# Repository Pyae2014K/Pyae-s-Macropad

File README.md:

# Pyae's Macropad

My macropad is a 13 key macropad with a rotary encoder.
It uses QMK firmware

It serves as a macropad that I can use every day.

## Features:
- EC11 Rotary encoder for volume
- 13 Keys, 12 for macros and 1 for swapping layers
- [VIA](https://www.caniusevia.com/) support

## PCB
My PCB was made using KiCad.

Schematic

PCB

I used [Joe Scotto's](https://www.youtube.com/@joe_scotto) footprints for all of them.

## CAD Model
Everything fits together using 4 M3 Bolts and heatset inserts.

It has 4 different pieces, Top Case, Bottom Case, Plate, and a Rotary Encoder Knob

This model was made in Fusion 360 by Autodesk.

## Firmware
This macropad uses [QMK](https://qmk.fm/) firmware for its code.
- 13 keys; 12 for macros, 1 for layers
- Rotary encoder used to change volume

## BOM:
Here is everything that is needed to make this macropad
| Qty | Part | Description |
|-----:|------|-------------|
| 1 | Seeed XIAO RP2040 | Microcontroller |
| 13 | MX-Style Switches | Mechanical keyboard switch |
| 13 | DSA Keycaps | DSA profile keycap |
| 14 | 1N4148 Diodes | DO-35 through-hole diode |
| 1 | EC11E Rotary Encoder | Rotary encoder |
| 4 | M3x16mm Screws | M3 screw |
| 4 | M3x5mx4mm Heatset Inserts | M3 threaded heat-set insert |
| 1 | Case Top | 3D printed top case |
| 1 | Case Bottom | 3D printed bottom case |
| 1 | Plate | Switch plate |
| 1 | Knob | Rotary encoder knob |

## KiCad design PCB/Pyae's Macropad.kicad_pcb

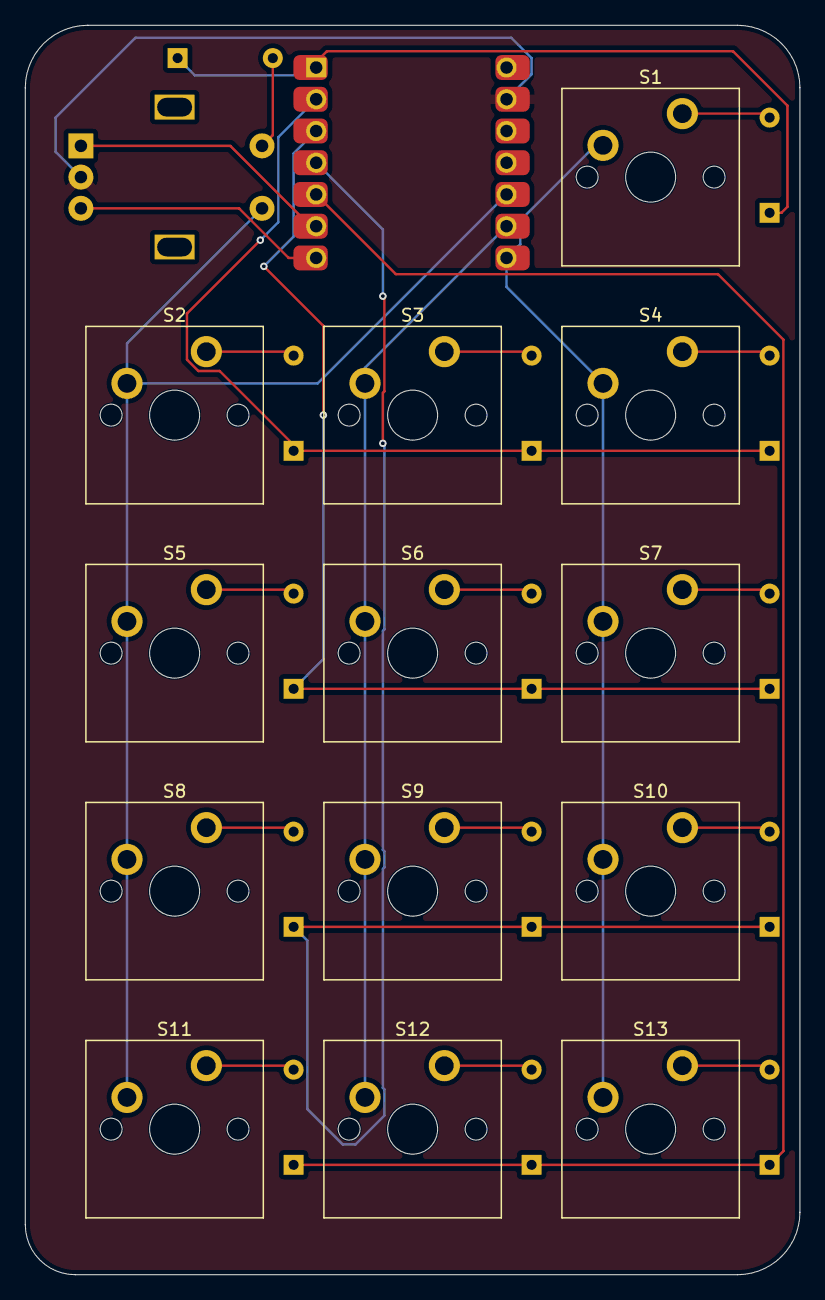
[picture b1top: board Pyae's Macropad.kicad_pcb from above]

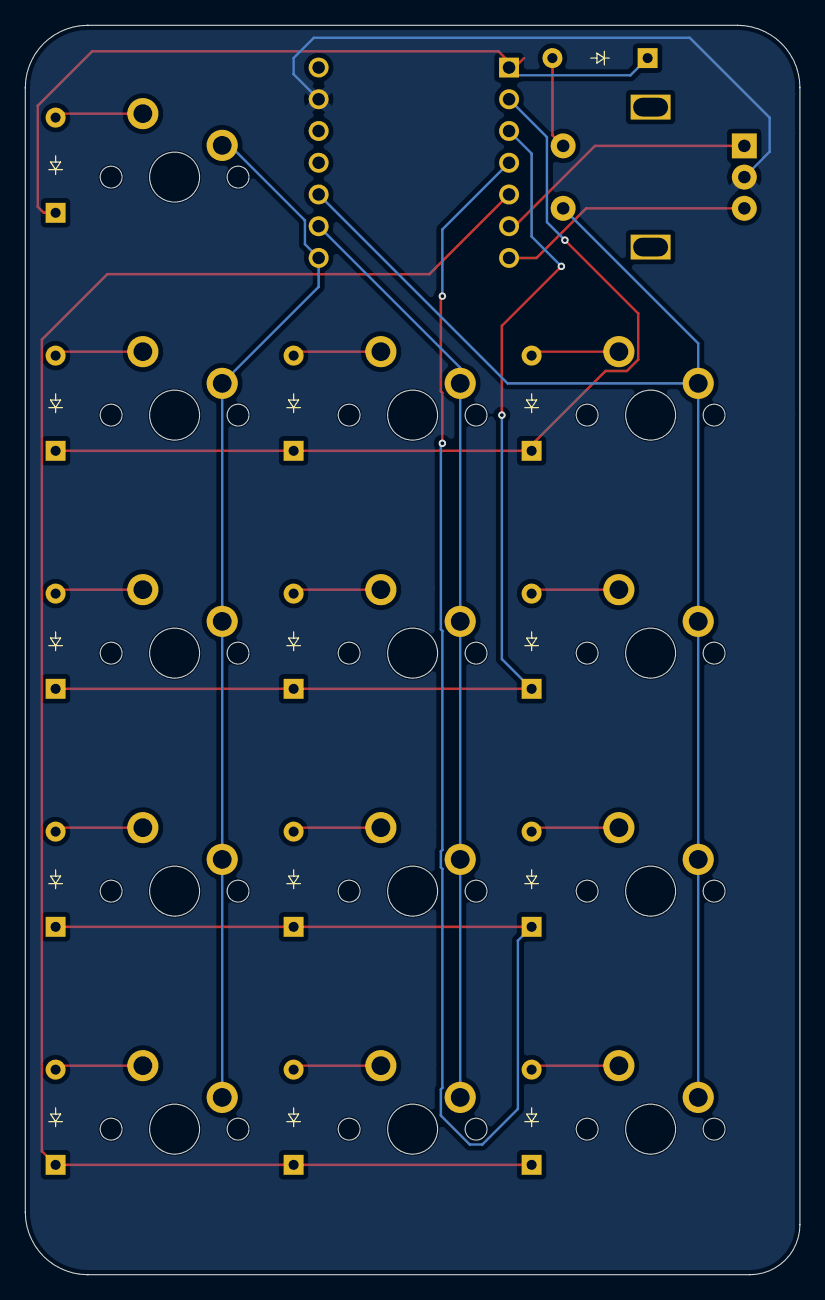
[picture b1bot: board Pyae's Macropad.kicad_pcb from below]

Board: 2 copper layers, 62.0 x 100.0 mm, 29 parts (14 on the bottom side), 25 nets.

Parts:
D1, D2, D3, D4, D5, D6, D7, D8, D9, D10, D11, D12, D13, D14: Diode_DO-35
S1, S2, S3, S4, S5, S6, S7, S8, S9, S10, S11, S12, S13: MX_PCB_1.00u
SW1: RotaryEncoder_Switch; Encoder_EC11_MX
U1: MOUDLE-SEEEDUINO-XIAO; Seeed_XIAO_RP2040

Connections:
A: SW1.A, U1.6 (PA9_A5_D5_SCL)
B: SW1.B, U1.7 (PB08_A6_D6_TX)
Col0: S2.1, S5.1, S8.1, S11.1, SW1.S1, U1.10 (PA5_A9_D9_MISO)
Col1: S3.1, S6.1, S9.1, S12.1, U1.9 (PA7_A8_D8_SCK)
Col2: S1.1, S4.1, S7.1, S10.1, S13.1, U1.8 (PB09_A7_D7_RX)
GND: SW1.C, U1.13 (GND)
unnamed: D2.2 (A), S1.2
unnamed: D3.2 (A), S2.2
unnamed: D4.2 (A), S3.2
unnamed: D5.2 (A), S4.2
unnamed: D6.2 (A), S5.2
unnamed: D7.2 (A), S6.2
unnamed: D8.2 (A), S7.2
unnamed: D9.2 (A), S8.2
unnamed: D10.2 (A), S9.2
unnamed: D11.2 (A), S10.2
unnamed: D12.2 (A), S11.2
unnamed: D13.2 (A), S12.2
unnamed: D14.2 (A), S13.2
Row0: D1.1 (K), D2.1 (K), U1.1 (PA02_A0_D0)
Row1: D3.1 (K), D4.1 (K), D5.1 (K), U1.2 (PA4_A1_D1)
Row2: D6.1 (K), D7.1 (K), D8.1 (K), U1.3 (PA10_A2_D2)
Row3: D9.1 (K), D10.1 (K), D11.1 (K), U1.4 (PA11_A3_D3)
Row4: D12.1 (K), D13.1 (K), D14.1 (K), U1.5 (PA8_A4_D4_SDA)
S2: D1.2 (A), SW1.S2

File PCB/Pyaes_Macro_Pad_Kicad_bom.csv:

Designator,Footprint,Quantity,Value,LCSC Part #
"D1, D10, D11, D12, D2, D3, D4, D5, D6, D7, D8, D9",Diode_DO-35,12,~,
J2,OLED_128x32,1,OLED_DISPLAY,
"S1, S10, S11, S12, S2, S3, S4, S5, S6, S7, S8, S9",MX_PCB_1.00u,12,~,
SW13,Encoder_EC11_MX,1,RotaryEncoder_Switch,
U1,Seeed_XIAO_RP2040,1,MOUDLE-SEEEDUINO-XIAO,

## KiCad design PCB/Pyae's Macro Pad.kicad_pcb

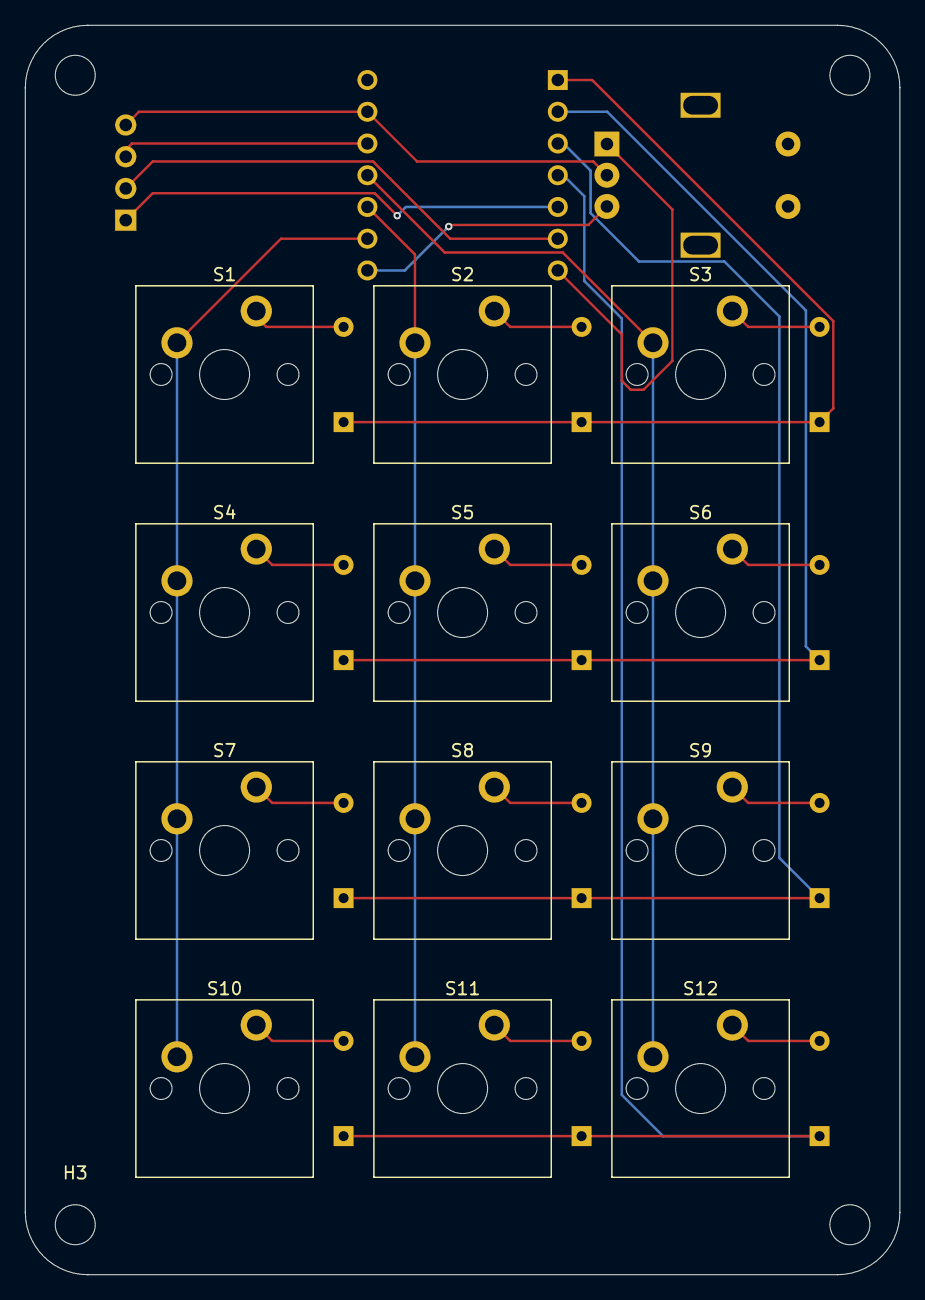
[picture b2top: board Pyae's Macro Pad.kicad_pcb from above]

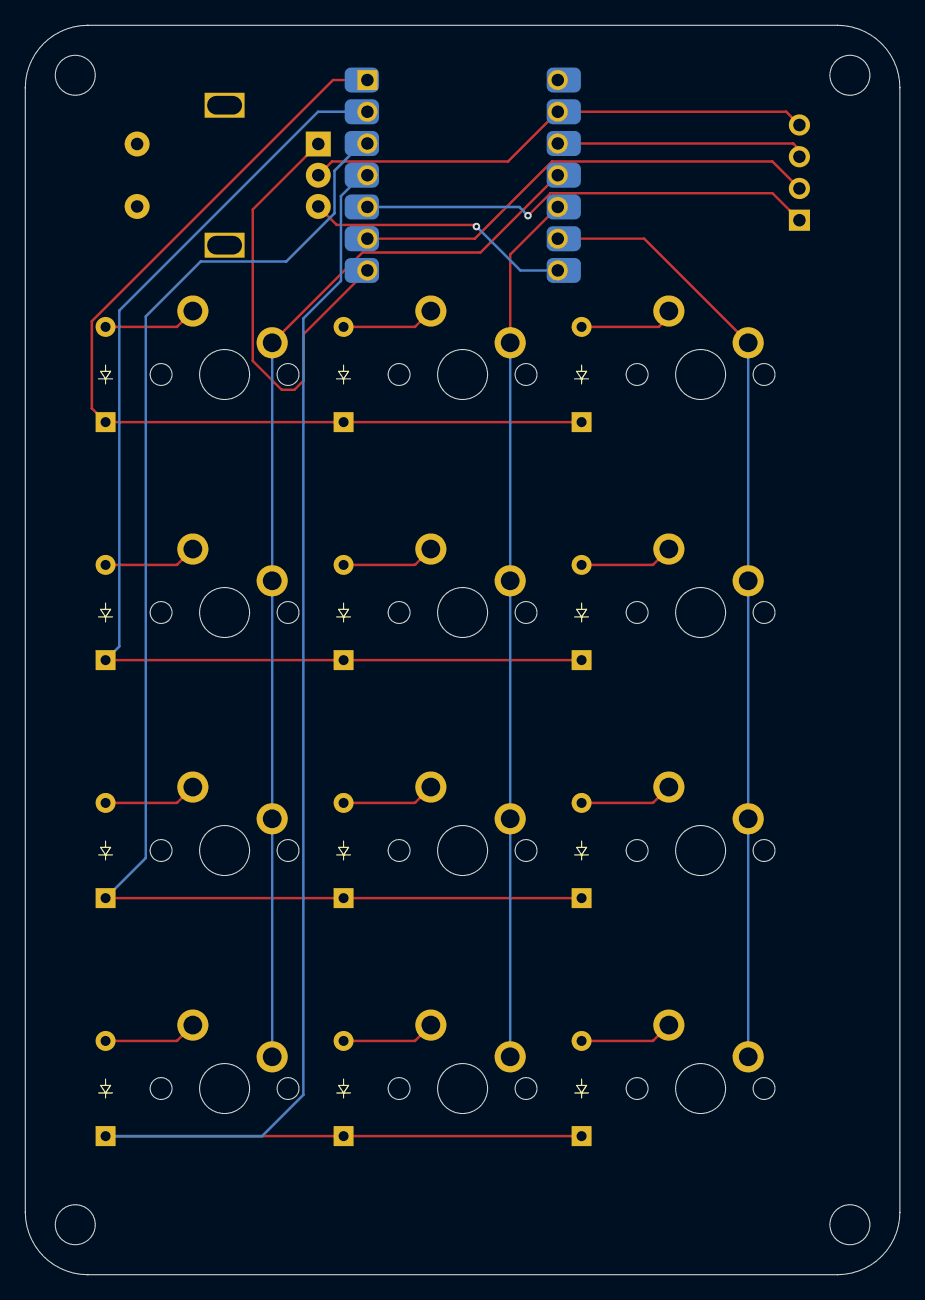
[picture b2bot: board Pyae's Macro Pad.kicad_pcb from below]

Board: 2 copper layers, 70.0 x 100.0 mm, 31 parts (13 on the bottom side), 25 nets.

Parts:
D1, D2, D3, D4, D5, D6, D7, D8, D9, D10, D11, D12: Diode_DO-35
H1, H2, H3, H4: MountingHole; MountingHole_3.2mm_M3
J2: OLED_DISPLAY; OLED_128x32
S1, S2, S3, S4, S5, S6, S7, S8, S9, S10, S11, S12: MX_PCB_1.00u
SW13: RotaryEncoder_Switch; Encoder_EC11_MX
U1: MOUDLE-SEEEDUINO-XIAO; Seeed_XIAO_RP2040

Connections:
/COL0: S1.1, S4.1, S7.1, S10.1, U1.9 (PA7_A8_D8_SCK)
/COL1: S2.1, S5.1, S8.1, S11.1, U1.10 (PA5_A9_D9_MISO)
/COL2: S3.1, S6.1, S9.1, S12.1, U1.11 (PA6_A10_D10_MOSI)
/EC11A: SW13.A, U1.7 (PB08_A6_D6_TX)
/EC11B: SW13.B, U1.8 (PB09_A7_D7_RX)
/OLED_SCL: J2.2, U1.6 (PA9_A5_D5_SCL)
/OLED_SDA: J2.1, U1.5 (PA8_A4_D4_SDA)
/ROW0: D1.1 (K), D2.1 (K), D3.1 (K), U1.1 (PA02_A0_D0)
/ROW1: D4.1 (K), D5.1 (K), D6.1 (K), U1.2 (PA4_A1_D1)
/ROW2: D7.1 (K), D8.1 (K), D9.1 (K), U1.3 (PA10_A2_D2)
/ROW3: D10.1 (K), D11.1 (K), D12.1 (K), U1.4 (PA11_A3_D3)
GND: J2.4, SW13.C, U1.13 (GND)
unnamed: D1.2 (A), S1.2
unnamed: D2.2 (A), S2.2
unnamed: D3.2 (A), S3.2
unnamed: D4.2 (A), S4.2
unnamed: D5.2 (A), S5.2
unnamed: D6.2 (A), S6.2
unnamed: D7.2 (A), S7.2
unnamed: D8.2 (A), S8.2
unnamed: D9.2 (A), S9.2
unnamed: D10.2 (A), S10.2
unnamed: D11.2 (A), S11.2
unnamed: D12.2 (A), S12.2
VCC: J2.3, U1.12 (3V3)

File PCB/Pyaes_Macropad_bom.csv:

Designator,Footprint,Quantity,Value,LCSC Part #
"D1, D10, D11, D12, D13, D14, D2, D3, D4, D5, D6, D7, D8, D9",Diode_DO-35,14,~,
"S1, S10, S11, S12, S13, S2, S3, S4, S5, S6, S7, S8, S9",MX_PCB_1.00u,13,~,
SW1,Encoder_EC11_MX,1,RotaryEncoder_Switch,
U1,Seeed_XIAO_RP2040,1,MOUDLE-SEEEDUINO-XIAO,
